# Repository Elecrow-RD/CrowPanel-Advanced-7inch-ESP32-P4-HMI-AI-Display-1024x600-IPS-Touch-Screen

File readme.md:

### 1, Product picture

### 2, Product version number

|      | Hardware | Software | Remark |
| ---- | -------- | -------- | ------ |
| 1    | V1.0     | V1.0     | old |
| 1    | V1.1     | V1.1     | old |
| 1    | V1.2     | V1.2     | latest |

**Version 1.1 Update**

The C6 module version 1.1 adds support for 4-wire SDIO communication. Additionally, the arrangement of the SDIO pins has been adjusted, with the pin mappings of the data lines D0–D3 changing from **IO14, IO15, IO16, IO17** to **IO17, IO16, IO15, IO14**. 

**Version 1.2 Update** 

Based on the V1.1 version, V1.2 further optimized the communication stability of the LoRa wireless module. At the same time, the signal pins of the wireless module socket were re-allocated: the original **IO53 and IO54** were adjusted to **IO27 and IO28** respectively, and correspondingly, **IO27 and IO28** were adjusted to **IO53 and IO54** respectively.

### 3, product information

| **Main Chip-ESP32-P4NRW32**                  |                                                              |
| -------------------------------------------- | ------------------------------------------------------------ |
| CPU/SoC                                      | **ESP32-P4**RISC-V 32-bit dual-core processor for HP systems, running at up to 400 MHz;RISC-V 32-bit single-core processor for LP systems, running at up to 40 MHz |
| System Memory                                | 768 KB L2MEM (HP) 32 KB SRAM (LP) 8 KB TCM 32 MB PSRAM       |
| Memory                                       | 128 KB ROM (HP) 16 KB ROM (LP) 16 MB Flash                   |
| Development Environment                      | ESP-IDF、Arduino IDE                                   |
| **Screen**                                   |                                                              |
| Size                                         | 7.0 inch                                                     |
| Resolution                                   | 1024*600                                                     |
| Display Panel                                | IPS Panel                                                    |
| Touch Panel                                  | Capacitive Touch, Single/5-point Touch                       |
| Viewing Angle                                | 178°                                                         |
| Brightness                                   | 400 cd/m²(Typ.)                                              |
| Color Depth                                  | 16.7M (8-bit)                                                |
| **Wireless Communication - Onboard Antenna** |                                                              |
| WiFi                                         | Support 2.4GHz(Wi-Fi6), 802.11a/b/g/n                        |
| Bluetooth                                    | Support Bluetooth 5.3 and BLE                                |
| Other                                        | Zigbee, LoRa, nRF2401, Matter, Thread (**Optional**)         |
| **Interface/Function**                       |                                                              |
| Interface                                    | USB2.0, UART, I2C, GPIO female headers, SD card holder, battery socket, speaker jack, camera header, module female headers, etc. |
| Function                                     | Audio amplifier, battery charge management, USB to UART, dual microphones, dual speakers etc. |
| **Button/LED Indicator**                     |                                                              |
| Reset Button                                 | Yes, press to reset the device                               |
| Boot Button                                  | Yes, press and hold the power button to burn the program     |
| Power Button                                 | Switch On/Off                                                |
| PWR                                          | Device power on/off indication                               |
| CHG                                          | Lithium battery charging status, Low battery state           |
| **Other**                                    |                                                              |
| Installation method                          | All around mounting holes(M3 3.2mm), embedded, shell assembly |
| Operating temperature                        | -20~70 °C                                                    |
| Storage temperature                          | -30~80 °C                                                    |
| Power Input                                  | 5V/2A, USB or UART terminal                                  |
| Active Area                                  | 155mm*87mm                                                   |
| Dimensions                                   | 180*105mm                                                    |

### Functional description of the product's internal interfaces:

| Pin Name | Description                                                  | Connector Type |
| :------- | :----------------------------------------------------------- | :------------- |
| SPK      | Output audio signals to connect to speakers. The main board comes with a power amplifier chip circuit. | PH2.0-2P       |
| PWR      | Power LED.                                                   |                |
| RST      | Reset button. Press it to reset the system.                  |                |
| boot     |                                                              |                |
| UART1    | Builds communication between Logic modules, including the serial communication module and the print module. | HY2.0-4P       |
| I2C      | Builds communication between Logic modules, including the serial communication module and the print module. | HY2.0-4P       |
| UART3-IN | Input power supply and serial communication functionality    | XH2.54-4P      |
| BAT      | Connect the lithium battery. (with battery charging circuit) | PH2.0-2P       |

### 4, Use the driver module

| Name | dependency library |
| ---- | ------------------ |
| LVGL | lvgl/lvgl@9.2   |

### 5,Quick Start

##### ESP-IDF starts

1.Right-click on an empty space in the project folder and select "Open with VS Code" to open the project.

2.In the IDF plug-in, select the port, then compile and flash

### 6,Folder structure.
|--3D file： Contains 3D model files (.stp) for the hardware. These files can be used for visualization, enclosure design, or integration into CAD software.

|--Datasheet: Includes datasheets for components used in the project, providing detailed specifications, electrical characteristics, and pin configurations.

|--Eagle_SCH&PCB: Contains **Eagle CAD** schematic (`.sch`) and PCB layout (`.brd`) files. These are used for circuit design and PCB manufacturing.

|--example: Provides example code and projects to demonstrate how to use the hardware and libraries. These examples help users get started quickly.

|--factory_firmware: Stores pre-compiled factory firmware that can be directly flashed onto the device. This ensures the device runs the default functionality.

|--factory_sourcecode:  Contains the source code for the factory firmware, allowing users to modify and rebuild the firmware as needed.

|--libraries: Includes necessary libraries required for compiling and running the project. These libraries provide drivers and additional functionalities for the hardware.

### 7,Pin definition

#### ESP32-P4 7 inch and IPS Display Wiring Pins:
**DSI = Display Serial Interface**is a high-speed, low-power display interface standard defined by the MIPI Alliance, most commonly used in smartphones, tablets, Raspberry Pi devices, and embedded Linux systems.

DSI Pin connection

DSI_DATAN0--IO40

DSI_DATAN0--IO39

DSI_DATAN0--IO36

DSI_DATAN0--IO35

DSI_CLKN--IO37

DSI_CLKP--IO38

DSI_REXT--IO34

#### ESP32-P4 and Touch Driver Wiring：

i2c address: 0x5D/0x14.(The INT pin level during reset of the GT911 touch chip determines the device address.)

INT Low Level(0x5D);

INT High Level(0x14).

Pin connection

I2C1_SCL(IO46)

I2C1_SDA(IO45)

INT_TP(IO42)

RESET_TP(IO40)

#### ESP32-P4 and wireless module wiring pins：

Output voltage: 3.3V Output current: 1A max. Use: The power supply communicates with the wireless module.

Pin connection

#define RADIO_GPIO_CLK 8

#define RADIO_GPIO_MISO 7

#define RADIO_GPIO_MOSI 6

#ifdef CONFIG_BSP_SX1262_ENABLED

#define SX1262_GPIO_BUSY 9

#define SX1262_GPIO_IRQ 53

#define SX1262_GPIO_NRST 54

#define SX1262_GPIO_NSS 10

#ifdef CONFIG_BSP_NRF2401_ENABLED

#define NRF24_GPIO_IRQ 9

#define NRF24_GPIO_CE 53

#define NRF24_GPIO_CS 54

ESP32-P4 and Audio out：

Pin connection

#define AUDIO_GPIO_LRCLK    21   // GPIO pin number for LRCLK (Left-Right Clock)

#define AUDIO_GPIO_BCLK     22   // GPIO pin number for BCLK (Bit Clock)

#define AUDIO_GPIO_SDATA    23   // GPIO pin number for SDATA (Serial Data)

#define AUDIO_GPIO_CTRL     30   // GPIO pin number for audio amplifier control

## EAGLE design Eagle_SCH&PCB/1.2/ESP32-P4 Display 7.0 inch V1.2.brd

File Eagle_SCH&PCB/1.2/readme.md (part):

# ESP32-P4 7.0-Inch Display Product Hardware Driver Guide

| Document Attribute | Details |
| --- | --- |
| Document Version | V1.0 |
| Applicable Hardware | ESP32-P4 Display 7.0 inch V1.2 |
| Baseline Date | 2026-07-29 |
| Schematic Date | 2026-05-05 (drawing frame date) |
| Author | OpenAI Codex (compiled from project schematics and validated examples) |
| Document Status | Suitable for hardware maintenance, driver porting, and onboarding handoff |

## 1. Document Scope and Evaluation Criteria

This document cross-checks the following evidence within the project:

1. `1.2/ESP32-P4 Display 7.0 inch V1.2.sch`: EAGLE 9.6.2 schematic source file, used as the primary evidence for components, nets, and electrical connections.
2. `1.2/ESP32-P4 Display 7.0 inch V1.2.pdf`: Single-page full-board schematic, used as visual verification evidence for functional sections, populated/NC markings, and graphical connections.
3. `idf-code/Lesson01` through `Lesson17`: ESP-IDF examples organized by function, used as the primary evidence for working software configurations.
4. The `idf_component.yml`, `Kconfig`, header files, and BSP source files for each example: used as evidence for versions, default values, and build dependencies.

The evidence priority is as follows:

`Effective constants/initialization parameters in working code` > `Kconfig defaults or comments in the same directory` > `V1.2 schematic nets` > `general README`.

When the code and schematic are inconsistent, this document uses the code as the current runtime baseline as required and lists the discrepancies in Section 15. Here, “validated” means that the repository provides the function as a standalone lesson example; it does not mean that the hardware was reconnected and electrically tested during the generation of this document. The repository does not include complete `sdkconfig` files, build artifacts, or test logs, so final values that depend on menuconfig must still be fixed in the production project.

## 2. Product Hardware Architecture

The product uses the ESP32-P4NRW32 as the main application controller, while the ESP32-C6-MINI-1-N4 provides Wi-Fi/wireless coprocessing capabilities. The main controller connects directly to the 7-inch MIPI-DSI display, MIPI-CSI camera interface, touch I2C, SDMMC, PDM microphone, I2S amplifiers, USB 2.0, and UART/I2C/GPIO expansion interfaces. The board also includes an STC8H1K08 for auxiliary control functions such as charging-status and battery monitoring.

The main onboard power paths include USB/5 V input, battery charging and power switching, 5 V-to-3.3 V conversion, 5 V-to-1.2 V conversion, a 3.3 V audio LDO, 2.8 V/1.8 V camera LDOs, LCD power, and a boost/constant-current backlight driver.

## 3. Peripheral Overview

| Category | Device/Interface | Key Connection or Model | Software Validation Status |
| --- | --- | --- | --- |
| Main controller | ESP32-P4NRW32 (U7) | External W25Q128JVSIQ, 40 MHz, 32.768 kHz | Validated; target of all ESP-IDF examples |
| Wireless coprocessor | ESP32-C6-MINI-1-N4 (IC1) | P4 GPIO47/48 UART; GPIO32 enable; C6 SDIO network present | Wi-Fi example available; underlying P4-C6 transport abstraction is not fully included in the repository |
| Display | 7.0-inch 1024x600 IPS + EK79007 | 2-lane MIPI-DSI, GPIO31 backlight | Validated |
| Touch | GT911 capacitive touch | I2C0 GPIO45/46, RST40, INT42 | Validated |
| Camera | SC2336 (software detection target)/24-pin CSI FPC | 2-lane MIPI-CSI, SCCB GPIO12/13 | Validated |
| Storage | W25Q128JVSIQ NOR Flash | Dedicated ESP32-P4 Flash pins | Boot storage, managed by ESP-IDF |
| Storage | MicroSD card socket | Schematic: SDMMC GPIO14..19; code: GPIO43/44/39 | Validated code differs from schematic; see Section 15 |
| Audio input | LMA3526B381-class PDM microphone (U176) | CLK24, DATA26, L/R20 | Validated |
| Audio output | Dual NS4168 (U13/U3) + dual speakers | I2S GPIO21/22/23, SD GPIO30 | Validated |
| Optional audio codec | ES7210 ADC, ES8311 DAC | Explicitly marked `NC` in schematic | Must not be enabled by default |
| USB Device | ESP32-P4 USB 2.0 D+/D- | Native TinyUSB HID | Validated |
| USB-to-UART | CH340K (U1) | Onboard download/debug channel | Fixed hardware function; no application driver |
| UART expansion | UART1/UART2/UART3 nets | GPIO47/48, 34/33, 27/28, etc. | UART2 code validated |
| I2C expansion | 4-pin I2C_OUT | GPIO45/46 level-shifted to 3.3 V through BSS138 | Bus driver validated |
| GPIO expansion | 2x12 J7 | GPIO2/3/4/5/25/49..54, 3.3 V/5 V/GND | No unified driver; available for peripheral reuse |
| Environmental sensor | DHT20 (external) | I2C 0x38, shared GPIO45/46 | Example validated; not an onboard device |
| LoRa | SX1262 (external) | SPI GPIO6/7/8 + control pins | TX/RX examples validated; control-pin version conflict exists |
| 2.4 GHz | nRF24 (external) | SPI GPIO6/7/8 + control pins | TX/RX examples validated; control-pin version conflict exists |
| Charging management | TP4059-SOT23-6 (U2) | 5 V, battery, CHG/STDBY status | Automatic hardware function; monitored by STC8 |
| Auxiliary MCU | STC8H1K08-36I (U14) | Charging LED, status, ADC_VBAT, UART | Present in schematic; repository contains no STC8 firmware |
| Power | MT3406 x2, MT9201, MT3608, ME6211 series | 3.3 V, 1.2 V, LCD/backlight, camera/audio power | Automatic hardware function/enable-pin controlled |
| Buttons/switches | BOOT K3, RESET K4, power slide switch SW1 | BOOT/CHIP_PU/power MOSFET | Fixed hardware function |
| Indicators | Charging/full/power LEDs | TP4059 + STC8/discrete logic | Repository contains no application-level LED driver |

## 4. ESP32-P4 GPIO Resource Table

The table below prioritizes the values actually used by the code; “Schematic Function” is provided to identify electrical connections.

| GPIO | Current Code Function | Direction/Multiplexing | Schematic Net/Electrical Connection | Conflict Notice |
| ---: | --- | --- | --- | --- |
| 6 | Wireless SPI MOSI | SPI output | Wireless interface series resistor | Shared by wireless modules |
| 7 | Wireless SPI MISO | SPI input | Wireless interface series resistor | Shared by wireless modules |
| 8 | Wireless SPI SCK | SPI output | Wireless interface series resistor | 8 MHz |
| 9 | SX1262 BUSY / nRF24 IRQ | Input/interrupt | Wireless interface | The two modules are mutually exclusive |
| 10 | SX1262 NSS | Push-pull output | Wireless interface | nRF24 code does not use this pin |
| 11 | Camera RESET net | GPIO output through level shifter | `IO11_CSI_RESET` | Current camera code instead configures `reset_pin=-1` |
| 12 | Camera SCCB SDA | I2C open-drain | `I2C2_SDA` through BSS138 | Code enables internal pull-up |
| 13 | Camera SCCB SCL | I2C open-drain | `I2C2_SCL` through BSS138 | 100 kHz |
| 14..19 | Onboard SDMMC D3/D2/D1/D0/CLK/CMD in schematic | SDMMC | Directly connected to SD card nets | Not used by current SD code |
| 20 | PDM microphone L/R selection | GPIO/strap | `MIC_L/R` | Current code does not actively set it; channel is determined by hardware resistor |
| 21 | Audio LRCLK | I2S1 output | Dual NS4168 LRCLK | 16 kHz |
| 22 | Audio BCLK | I2S1 output | Dual NS4168 BCLK | Standard I2S |
| 23 | Audio SDATA | I2S1 output | Dual NS4168 SDATA | 16-bit stereo |
| 24 | PDM CLK | I2S0 output | PDM microphone CLK; also routed to optional codec MCLK | Occupied during recording |
| 26 | PDM DATA | I2S0 input | PDM microphone DATA | Occupied during recording |
| 27 | SX IRQ / UART TX (code) | Interrupt input/output | Schematic net is `P4_TXD2` | Conflicts with GPIO53 Kconfig default |
| 28 | SX RESET / nRF CS / UART RX (code) | Output/input | Schematic net is `P4_RXD2` | Multiple functions are mutually exclusive; conflicts with GPIO54 Kconfig default |
| 29 | LCD backlight power control | GPIO output | `LCD_BK_POWER`, Q11 marked NC | Not driven by current display code |
| 30 | Audio amplifier SD | Push-pull output, active-low enable | `AUDIO_OUT_SD` -> Q10 -> dual amplifier CTRL | Validated |
| 31 | LCD backlight brightness | LEDC PWM | `LCD_BK_EN` -> MT9201 EN | 30 kHz, 11-bit |
| 32 | ESP32-C6 EN | Push-pull output/reset | `C6_EN` | Requires attention when powering up the Wi-Fi subsystem |
| 33 | Expansion UART RX | UART input | `RXD3` through level shifter | UART_IN_RXD3 on the 5 V side |
| 34 | Expansion UART TX | UART output | `TXD3` through level shifter | UART_IN_TXD3 on the 5 V side |
| 37 | Debug/download TXD0 | UART output | `TXD0` | CH340K path |
| 38 | Debug/download RXD0 | UART input | `RXD0` | CH340K path |
| 39 | SD D0 (code) | SDMMC input/output | Schematic only shows `P4_IO39` through series resistor | Inconsistent with onboard SD schematic |
| 40 | GT911 RESET | Push-pull output, active-low | `RESET_TP` | Validated |
| 41 | LCD RESET | Push-pull output, active-low | `LCD_RESET` | Display driver sets `reset_gpio_num=-1`; handled by hardware/panel path |
| 42 | GT911 INT | Input/touch-address strap | `INT_TP` | Driver interrupt level configured as 0 |
| 43 | SD CLK (code) | SDMMC output | Schematic only shows `P4_IO43` | Inconsistent with onboard SD schematic |
| 44 | SD CMD (code) | SDMMC bidirectional | Schematic only shows `P4_IO44` | Inconsistent with onboard SD schematic |
| 45 | GT911/expansion I2C SDA | I2C0 open-drain | `I2C1_SDA`, through BSS138 to the 3.3 V side | Shared bus |
| 46 | GT911/expansion I2C SCL | I2C0 open-drain | `I2C1_SCL`, through BSS138 to the 3.3 V side | 400 kHz |
| 47 | ESP32-C6/UART2 TX | UART output | `TXD1` | 115200 8N1 example |
| 48 | ESP32-C6/UART2 RX | UART input | `RXD1` | 115200 8N1 example |
| 49..52 | J7 GPIO expansion | General-purpose GPIO | Directly connected to J7 | Pay attention to external loads |
| 53/54 | J7 GPIO / default wireless Kconfig control pins | General-purpose GPIO | Directly connected to J7 | Actual code headers do not use Kconfig values |

MIPI DSI, MIPI CSI, USB D+/D-, external Flash, crystal, and ESP32-P4 internal power pins are dedicated pins. They are not included in the general-purpose GPIO table and must not be repurposed as general-purpose I/O.

## 5. Main Controller, Boot, and External Flash

### 5.1 ESP32-P4NRW32

- Main controller: U7, ESP32-P4NRW32, RISC-V application processor.
- Software layer: ESP-IDF + FreeRTOS; the display/touch functions use Espressif Component Manager components.
- Minimum dependency: Multiple examples specify ESP-IDF `>=5.4.0`; the display lesson specifies `>=5.4.2`.
- Boot: K3 pulls `SPI_BOOT` low to enter download mode; K4 pulls `CHIP_PU` low to reset.
- Clocks: 40 MHz main crystal; 32.768 kHz low-speed crystal.

### 5.2 W25Q128JVSIQ

- The dedicated U7 `FLASH_CS/CK/WP/HOLD/D/Q` pins connect to the IC10 W25Q128JVSIQ.
- The driver is managed by the ESP-IDF ROM bootloader, SPI Flash driver, and partition table. It must not be reinitialized at the application layer using a general-purpose SPI driver.
- Partitions: Each lesson project includes its own `partitions.csv`; when porting to a unified product project, a single partition baseline must be selected.
- Risk: Do not reuse dedicated Flash pins. Before changing the Flash frequency/mode, verify `menuconfig` and the device capabilities.

## 6. Display and Backlight

### 6.1 EK79007 MIPI-DSI Display

| Parameter | Validated Code Value |
| --- | --- |
| Resolution | 1024 x 600 |
| Pixel format | RGB565, 16 bpp |
| DSI | bus 0, 2 data lanes, 900 Mbps/lane |
| DPI pixel clock | 51 MHz |
| Horizontal timing | BP 160, pulse 70, FP 160 |
| Vertical timing | BP 23, pulse 10, FP 12 |
| DBI commands | 8-bit command, 8-bit parameter, VC0 |
| Frame buffer | 1 panel FB; LVGL uses double buffering in SPIRAM |
| Rotation | No XY swap or mirroring |

Software dependencies: `esp_lcd_mipi_dsi`, `espressif/esp_lcd_ek79007 ^1.0.2`, `espressif/esp_lvgl_port ^2.6.0`, `lvgl ^8.3.11`, FreeRTOS.

Key configuration example:

```c
esp_lcd_dsi_bus_config_t bus = {
    .bus_id = 0,
    .num_data_lanes = 2,
    .lane_bit_rate_mbps = 900,
};
esp_lcd_dpi_panel_config_t dpi = {
    .dpi_clock_freq_mhz = 51,
    .pixel_format = LCD_COLOR_PIXEL_FORMAT_RGB565,
    .video_timing = { .h_size = 1024, .v_size = 600,
        .hsync_back_porch = 160, .hsync_pulse_width = 70, .hsync_front_porch = 160,
        .vsync_back_porch = 23, .vsync_pulse_width = 10, .vsync_front_porch = 12 },
};
```

Initialization sequence: backlight PWM initialization -> DSI bus -> DBI IO -> EK79007 panel reset/initialization -> LVGL port -> first-frame rendering -> turn on backlight. The code explicitly keeps the backlight off at the end of `display_init()`; the caller must subsequently invoke `set_lcd_blight()`.

### 6.2 Backlight

- GPIO31, GPIO push-pull + LEDC low-speed channel 0, timer 0.
- 30 kHz, 11-bit, PLL divided clock.
- The brightness interface accepts 0..100; the actual nonzero duty is `brightness * 18 + 200`, so it is not a strict percentage.
- Electrical path: GPIO31 -> MT9201 EN/dimming path -> DSI LED driver; the schematic specifies an LED current of approximately 182 mA (`200 mV / 1.1 ohm`).
- Risk: Do not configure GPIO31 as a regular GPIO held high for extended periods and thereby bypass the PWM constraints. Changing the backlight current requires modifying the hardware sense resistor, not merely changing the duty cycle.

## 7. GT911 Touch

- GPIO45 SDA, GPIO46 SCL, I2C master port 0, 7-bit address.
- Bus frequency: 400 kHz; I2C glitch filter: 7 cycles. The code enables the SoC internal pull-ups, while the schematic also includes level shifting/external pull-up networks.
- GPIO40 RESET, active-low; GPIO42 INT, with the driver configured for interrupt level=0.
- Resolution bounds: 1024x600; no XY swap or mirroring.
- Address: First uses `ESP_LCD_TOUCH_IO_I2C_GT911_ADDRESS`; if that fails, it tries `..._ADDRESS_BACKUP`, supporting both GT911 address-strap states.
- Software layer: ESP-IDF new I2C master API, `esp_lcd_panel_io_i2c`, `esp_lcd_touch_gt911`, FreeRTOS.

Initialization sequence: `i2c_init()` -> create panel I/O -> `esp_lcd_touch_new_i2c_gt911()` -> periodically call `touch_read()`. The USB HID example reads at 10 ms intervals, corresponding to an application sampling rate of 100 Hz.

Note: Before switching to the backup address after a failure, the current code does not delete the panel I/O handle created during the first attempt. For long-term maintenance, unified failure cleanup is recommended; this issue does not change the existing working parameters.

## 8. MIPI-CSI Camera

### 8.1 Electrical Connections

- 24-pin FPC3, 2-lane MIPI-CSI: D0+/D0-, D1+/D1-, CLK+/CLK-.
- SCCB: GPIO12 SDA, GPIO13 SCL, through BSS138 level shifting.
- Schematic: GPIO11 connects to `CSI_RESET` through a level shifter; the FPC also provides XVCLK, AVDD_2V8, and DOVDD_1V8.
- Software identification/tuning file: SC2336, 50 Hz anti-flicker.

### 8.2 Driver Configuration

- SCCB master port 1, 100 kHz, with internal pull-ups enabled.
- `esp_video_init()` reuses the previously created I2C bus handle.
- `reset_pin=-1`, `pwdn_pin=-1`; the current code does not operate the GPIO11 reset shown in the schematic.
- V4L2 device: `ESP_VIDEO_MIPI_CSI_DEVICE_NAME`, opened as nonblocking and read-only.
- Output format: forced to RGB565; the resolution is negotiated by the current sensor/V4L2 mode and is not hard-coded in the BSP.
- Two cache-aligned SPIRAM user-pointer buffers using V4L2 `REQBUFS/QUERYBUF/QBUF`; the capture task is pinned to core 0 at priority 3.
- Software dependencies: `esp_cam_sensor ^1.2.0`, `esp_sccb_intf ^0.0.5`, `esp_video ^1.1.0`, V4L2, LVGL, SPIRAM.

Initialization sequence: SCCB bus -> `esp_video_init()` -> open CSI device -> query/set RGB565 -> allocate and queue double buffers -> create LVGL canvas -> stream on.

Risk: Camera power and reset timing currently depend on board-level hardware/default driver behavior. If the sensor is replaced or intermittent detection failures occur during cold startup, add the GPIO11 reset sequence and a power-stabilization delay before attempting to increase the SCCB frequency.

## 9. SD Card

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
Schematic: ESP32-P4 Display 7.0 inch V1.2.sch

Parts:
C1, C2, C3, C17, C22, C69, C86, C102: 1uF; 0603
C4: 10uF/NC; 0603
C5, C7, C9, C36, C40, C41, C43, C45, C46, C50, C60, C61, C63, C72, C73, C108, C113, C115: 100nF; C0402
C6, C8, C42, C44, C47, C48, C49, C56, C71, C107, C112, C114, C116: 10uF; C0402
C10: 1uF; DISCRETE-NEW_C0603
C11, C15, C19, C20, C21, C35, C37, C52, C53, C54, C75, C76, C77, C80, C81, C82, C84, C144, C150, C151, C152, C155, C156, C159, C169: 100nF; 0603
C12, C27, C28, C32: 10uF/10V+; 0603
C13, C18: 22uF; C0805
C14, C16, C38, C74, C78, C79, C83, C136, C149, C153, C157: 10uF; 0603
C23, C24, C103, C104: 47uF; 0603
C25, C160, C161, C162, C163, C164, C165, C166, C167, C168: 10pF_NC; C0402
C26, C31: 22pF; 0603
C29, C30: 12pF; C0402
C33, C34: 15pF; C0402
C39, C130, C132, C145: 100nF_NC; C0402
C51, C55, C57, C58, C59, C64, C65, C66: 1uF; C0402
C62: 10nF; C0402
C67, C68, C85, C105, C106, C158: 1nF; 0603
C70: 10UF; 0603
C87: 15pF; 0603
C88: 10UF_NC; 0603
C89, C101: 22pF_NC; C0402
C90, C99, C110: 10uF/25V; 0603
C91, C100, C111: 100nF/50V; 0603
C92: 22uF/16V; C0805
C93: 10nF/25V; 0603
C94: 10uF/25V; C0402
C95: 100nF/50V; C0402
C96, C97: 1uF/25V; 0603
C98, C109: 1uF/50V; 0603
C117, C118, C119, C120, C121, C122, C123, C124, C125, C126, C127, C128, C129, C131, C133, C137, C138, C139, C140, C141, C142, C146: 1uF_NC; C0402
C134, C148: 47uF_NC; 0603
C135, C147, C154: 100nF_NC; 0603
C143: 1uF_NC; 0603
C170, C171, C172, C173, C174, C175, C176: NC; C0402
D1: KT-0603RYG; LED_KT-0603RYG
D2, D007, D10: DSS34; D_SOD123FL
D003: NC/DSS34; D_SOD123FL
D4, D008, D11: 1N5817WS; D_SOD323
D005, D012, D013, D015, D017, D018: LMBR140ET1G
D14: Red; LED0603
D016: MM1W18_18V; LMSZ5233BT1G
D020: LMSZ5233BT1G_-6V; LMSZ5233BT1G
FB2, FB3, FB10, FB11: 1K/磁珠; L0603
FB4, FB5, FB13: 0R/800mA_NC; L0402
FB6: 0R/800mA; L0402
FB7, FB8, FB9, FB12: 1K/磁珠_NC; L0603
FB14: 0R/800mA_NC; R0402
FB15, FB16: 0R/800mA_NC; L0603
FB17, FB18, FB19, FB20: 0R/800mA; L0603
FB21: 0R/800mA; L0805
FPC2: FPC-6PIN-0.5MM
FPC3: AFC24-S24FIA-00; FPC-SMD_P0.50-24P_QCHF-SM-H2.0
IC1: ESP32-C6-MINI-1-N4; ESP32C6MINI1N4
IC2: ME6211C18M5G-N; SOT95P282X145-5N
IC3: ME6211C28M5G-N; SOT95P282X145-5N
IC4: ME6211C18M5G-N_NC; SOT95P282X145-5N
IC5: ES7210_NC; QFN40P400X400X80-33N
IC6: ES8311_NC; QFN40P300X300X60-21N
IC7, IC8: ME6211C33M5G-N; SOT95P282X145-5N
IC10: W25Q128JVSIQ; SOIC127P790X216-8N
J1, J16: TYPEC-3.0-16P-SMD; USB-3.0TYPEC-SMD
J2, J13: HY2.0-4P-SMT; CONNECTOR_4P-SMD-2.0
J3, J4, J6: PH2.0WT-2PIN
J5: HOLDER-MICROSD-9P; 9P-SMD-W/-RING
J7: CONN_12X22X12-SMD1; 2X12-SMD1
J8: HC-PZ200-8.7L-1X4PZ1; TEST-PIN-4-2.0MM
J9, J11: HEADER-7P-18.28X2.5; H7-2.54-18.28X2.5X5MM
J10: XH2.54-4P-SMT; XH2.54-4P-SMD
J12, J14, J15, J18: THO-M3.25MM-HOLE; THO-M3.2*5MM-HOLE
J21: C23398852_30P_0.5MM_下接_FC-05A30P11H20
K3, K4: KEY-4.5X4.5; KEY-4.5X4.5-SMD
L1, L6: 2.2μH_C5179446; 1008(2520)
L2, L5: 4.7uH_C45385206_2.4A; 1008(2520)
L3: 0R; L0603
L4: NC; L0603
P1, P2, P3, P4, P5, P6, P7, P8, P9, P10, P11, P12, P13, P14, P15, P17, P18, P19, P20, P21, P24, P25, P26, P28, P31, P32, P33, P34, P35, P36, P37, P38, P39, P53, P54, P55, P56, P57, P63, P64, P65, P66, P67, P68, P77, P87, P88: TEST_PADPAD-1.5MM; TEST_PAD-1.5MM
Q1, Q2, Q4, Q6, Q7, Q8, Q9: BSS138W_SOT323; MOS_SOT323
Q3, Q5: NCE20P45Q; PDFN3333
Q10: AO3401; PMOS_SOT23
Q11: AO3401_NC; PMOS_SOT23
R1, R5, R9, R18, R53, R54, R61, R66, R67, R71, R77, R87, R91, R106, R116, R160, R180, R181: 10K; R0603@1
R2, R117, R139, R165: 100K; R0603@1
R3, R4, R17, R26, R47, R50, R96, R101: 5.1K; R0603@1
R6, R7, R8, R10, R13, R24, R55, R60, R65, R76, R103, R118, R119, R184, R188, R189: 0R; R0603@1
R11: 22.1K; R0603
R12, R19, R20, R36, R37, R38, R39, R40, R41, R42, R43, R44, R70, R80, R88, R89, R90, R92, R95, R99, R100, R102, R105, R109, R190: 0R; R0402
R14, R21: NC/499K; R0603
R15, R27, R28, R29, R30, R140: 10K; 0402
R16, R31, R32, R69: 2K; R0603-SP
R22, R45, R46, R51, R52, R56, R57, R58, R59, R62, R78: 4.7K; R0603@1
R23: 0R; C0402
R25: 0R; R0603-SP
R33: 10K_NC; 0402
R34, R48, R49, R133, R135, R136, R137, R138: 22R; 0402
R35: NC/10M; R0402
R63, R64, R68, R108, R122, R123: 100K; R0402
R72, R73: 10K_NC; R0402
R74, R93, R94, R97, R98: 2K; R0603@1
R75: 2K_NC; R0603@1
R79, R147, R185: OR_NC; R0603-SP
R81, R82, R83, R84, R85, R86: 51K; 0402
R104, R158: 4.02K; R0402
R107, R110, R111, R124, R125, R126, R128, R130, R146, R148, R161, R170, R177: 0R_NC; R0402
R112, R113, R114, R115, R129, R149: 22R; R0603@1
R120, R121: 5.1K_NC; R0603@1
R127, R162: 22R; R0402
R131, R171, R333: 10K; R0402
R132, R134: OR; R0402
R141, R142, R144, R145: OR_NC; R0402
R143: 51K; R0603-SP
R150, R151, R216, R217, R332: 0R; 0402
R152, R153, R154, R155, R156, R157: 100R; R0402
R159: 1.1R; R0603-SP
R163: NC; R0603-SP
R164: 39k; R0603@1
R166: 180K; R0603
R167: 12K; R0603
R168: 1.91K; R0402
R169: 1K; R0402
R172, R174: 220R; R0603
R173, R175: 51K; R0603@1
R178, R179: 20K_NC; R0603
R182: 0R; L0805
R186: 100k; R0603@1
R187: 10k; R0603@1
R210: NC/10K; R0603@1
SW1: switch_6pin; SWITCH_6PIN_2P
U1: CH340K; ESOP-10-EP-150MIL
U2: TP4059-SOT23-6; SOT23-6L
U3, U13: NS4168; NS4168-ESOP-8
U4: NS4263B; SOP16
U6: MT9201; COOPER_SOT23-6
U7: ESP32-P4NRW32; IC_ESP32-P4NRW32
U8: UMH3NTN; SOP65P210X100-6N
U9, U10: MT3406_C22462728; SOT95P280X145-5N
U14: STC8H1K08-36I; TSSOP20
U16: MT3608; SOT95P280X145-6N
U176: LMA3526B381; MIC-SMD_5P-L3.5-W2.7-P1.67
Y2: 40MHZ; X322540MPB4SI
Y3: 24Mhz; 24MHZ_1631-24003-BTKEYA
Y4: 32.768K; NORDIC_NRF_XTAL_3215_N

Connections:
3V3$: C2.2, U1.10 (V3)
13: R189.2, U14.3 (MISO/P1.4)
14: R188.2, U14.4 (SCLK/P1.5)
+5V_IN: D2.+, D4.+, J10.3, P66.P$1, R46.1, R51.1
+VBUS1: D10.+, D11.+, J1.A4, J1.A9, J1.B4, J1.B9, P1.P$1
+VBUS2: D007.+, D008.+, J16.A4, J16.A9, J16.B4, J16.B9, P87.P$1
ADC_AVDD_3V3: C132.1, C133.2, FB5.2, IC5.22 (VDDA), IC5.23 (VDDM)
ADC_DVDD_3V3: C130.1, C131.2, FB4.2, IC5.6 (VDDP), IC5.7 (VDDD), R73.1
ADC_VBAT: C158.2, R164.2, R186.1, U14.13 (P3.2/ADC10)
AGND: C102.2, C103.2, C104.2, C105.1, C106.1, C134.1, C143.1, C148.1, C154.2, FB19.2, FB21.2, J4.P$3, J4.P$4, R79.2, R143.1, R185.1, U4.2, U4.7, U4.15, U13.7 (GND), U13.9 (PE)
AGND1: C72.1, C117.1, C118.1, C119.1, C120.1, C121.1, C122.1, C127.2, C128.2, C129.2, C132.2, C133.1, C137.1, C138.2, C139.2, C142.2, IC5.21 (GNDA), IC6.10 (AGND), R144.1, R145.2, R171.2, R182.2, U176.5_1 (5), U176.5_2 (5)
AGND3: C22.2, C23.2, C24.2, C67.1, C68.1, FB20.2, J6.P$3, J6.P$4, U3.7 (GND), U3.9 (PE)
AUDIO_CTRL: Q10.3 (D), R117.2, R139.2
AUDIO_OUT_5V: C134.2, C148.2, C154.1, FB15.2, U4.4, U4.13
AUDIO_OUT_SD: Q10.1 (G), R71.1, R147.1, U7.60 (GPIO30)
AUDIO_VDD1: C102.1, C103.1, C104.1, FB17.1, U13.6 (VDD)
AUDIO_VDD2: C22.1, C23.1, C24.1, FB18.1, U3.6 (VDD)
AUDIO_VDD_3V3: C152.2, C153.2, FB4.1, FB5.1, FB6.1, FB14.1, FB16.2, IC7.5 (VOUT)
AVDD_2V8: C82.2, C83.2, FPC3.1, FPC3.2, IC3.5 (VOUT)
C6_EN: C15.1, IC1.8 (EN), P37.P$1, R77.1, U7.63 (GPIO32)
C6_IO8: IC1.22 (IO8), R87.2
C6_IO9_BOOT: IC1.23 (IO9), P36.P$1
C6_RXD0: IC1.30 (RXD0), P21.P$1
C6_SD2_CLK: C25.2, IC1.25 (IO19), R34.2, R82.2
C6_SD2_CMD: C160.2, IC1.24 (IO18), R81.2, R133.2
C6_SD2_D0: C161.2, IC1.26 (IO20), R83.2, R135.2
C6_SD2_D1: C162.2, IC1.27 (IO21), R84.2, R136.2
C6_SD2_D2: C163.2, IC1.28 (IO22), R85.2, R137.2
C6_SD2_D3: C164.2, IC1.29 (IO23), R86.2, R138.2
C6_TXD0: IC1.31 (TXD0), P25.P$1
C6_VDD_3V3: C11.1, C14.2, IC1.3 (3V3), R76.1, R77.2, R81.1, R82.1, R83.1, R84.1, R85.1, R86.1, R87.1
CODEC_3V3: C145.1, C146.2, FB13.2, FB14.2, IC6.3 (PVDD), IC6.4 (DVDD)
CSID0_P: R153.1, U7.43 (CSI_DATAP0)
CSI_CLK_N: FPC3.19, R156.2
CSI_CLK_P: FPC3.18, R157.2
CSI_D0_N: FPC3.16, R152.2
CSI_D0_P: FPC3.15, R153.2
CSI_D1_N: FPC3.22, R154.2
CSI_D1_P: FPC3.21, R155.2
CSI_RESET: FPC3.8, Q4.2 (S), R57.2
CSI_SCL: FPC3.4, Q7.2 (S), R62.2
CSI_SDA: FPC3.5, Q6.2 (S), R56.2
DA1: J5.8 (DATA1), P56.P$1, R15.1
DA2: J5.1 (DATA2), P53.P$1, R30.1
DOVDD_1V8: C77.2, C78.2, C84.2, C85.2, FPC3.9, IC2.5 (VOUT), Q4.1 (G), Q6.1 (G), Q7.1 (G), R56.1, R57.1, R62.1, R67.2, Y3.4 (4_VDD)
DOWNLOAD_BOOT: R60.1, R106.2
DSI_CLK_N: J21.18, R100.1
DSI_CLK_P: J21.17, R102.1
DSI_DATA0_N: J21.24, R190.1
DSI_DATA0_P: J21.23, R92.1
DSI_DATA1_N: J21.21, R95.1
DSI_DATA1_P: J21.20, R99.1
DTR: R5.2, U1.4 (DTR#), U8.4 (E2)
EN_DCDC: R13.2, U7.79 (EN_DCDC)
ESP32_LDO1: C58.1, R105.2, U7.71 (VFB1/VO1)
ESP32_LDO2: C57.1, R40.2, U7.72 (VFB2/VO2)
ESP32_LDO3: C59.1, R80.2, U7.73 (VFB3/VO3)
ESP32_LDO4: C66.1, R109.2, U7.74 (VFB4/VO4)
FB_DCDC: C31.1, R14.2, R21.1, R103.1, U10.5 (FB)
FLASH_CK: IC10.6 (CLK), U7.32 (FLASH_CK)
FLASH_CS: IC10.1 (/CS), R333.1, U7.27 (FLASH_CS)
FLASH_D: IC10.5 (DI_(IO0)), U7.33 (FLASH_D)
FLASH_HOLD: IC10.7 (/HOLD_OR_/RESET_(IO3)), U7.31 (FLASH_HOLD)
FLASH_Q: IC10.2 (DO_(IO1)), U7.28 (FLASH_Q)
FLASH_WP: IC10.3 (/WP_(IO2)), U7.29 (FLASH_WP)
GND: C1.1, C2.1, C3.1, C4.1, C5.2, C6.1, C7.2, C8.1, C9.2, C10.1, C11.2, C12.2, C13.2, C14.1, C15.2, C16.1, C17.1, C18.2, C19.2, C20.1, C21.1, C25.1, C27.1, C28.2, C29.2, C30.2, C32.1, C33.2, C34.1, C35.1, C36.2, C37.1, C38.1, C39.2, C40.2, C41.2, C42.1, C43.2, C44.1, C45.2, C46.2, C47.1, C48.1, C49.1, C50.2, C51.2, C52.1, C53.1, C54.1, C55.2, C56.1, C57.2, C58.2, C59.2, C60.2, C61.2, C62.2, C63.2, C64.2, C65.2, C66.2, C69.1, C70.2, C71.1, C73.2, C74.1, C75.1, C76.1, C77.1, C78.1, C79.1, C80.1, C81.1, C82.1, C83.1, C84.1, C85.1, C86.1, C87.1, C88.2, C90.2, C91.2, C92.2, C94.2, C95.2, C98.2, C99.2, C100.2, C107.1, C108.2, C109.2, C110.2, C111.2, C112.1, C113.2, C114.1, C115.2, C116.1, C130.2, C131.1, C136.1, C144.1, C145.2, C146.1, C149.1, C150.1, C151.1, C152.1, C153.1, C155.1, C156.1, C157.1, C158.1, C159.1, C160.1, C161.1, C162.1, C163.1, C164.1, C165.1, C166.1, C167.1, C168.1, C169.2, C170.1, C171.1, C172.1, C173.1, C174.1, C175.1, C176.1, D14.-, D016.2, D018.1, D020.1, FB19.1, FB20.1, FB21.1, FPC2.4, FPC2.7, FPC2.8, FPC3.3, FPC3.6, FPC3.10, FPC3.12, FPC3.17, FPC3.20, FPC3.25, FPC3.26, IC1.1 (GND_1), IC1.2 (GND_2), IC1.11 (GND_3), IC1.14 (GND_4), IC1.36 (GND_5), IC1.37 (GND_6), IC1.38 (GND_7), IC1.39 (GND_8), IC1.40 (GND_9), IC1.41 (GND_10), IC1.42 (GND_11), IC1.43 (GND_12), IC1.44 (GND_13), IC1.45 (GND_14), IC1.46 (GND_15), IC1.47 (GND_16), IC1.48 (GND_17), IC1.49 (GND_18), IC1.50 (GND_19), IC1.51 (GND_20), IC1.52 (GND_21), IC1.53 (GND_22), IC1.54 (GND_23), IC1.55 (GND_24), IC1.56 (GND_25), IC1.57 (GND_26), IC1.58 (GND_27), IC1.59 (GND_28), IC1.60 (GND_29), IC1.61 (GND_30), IC2.2 (VSS), IC3.2 (VSS), IC4.2 (VSS), IC5.8 (GNDD), IC5.33 (EP), IC6.5 (DGND), IC6.20 (CE), IC6.21 (EP), IC7.2 (VSS), IC8.2 (VSS), IC10.4 (GND), J1.A1, J1.A12, J1.B1, J1.B12, J1.P$1, J1.P$2, J1.P$3, J1.P$4, J2.4, J2.SS1, J2.SS2, J3.P$2, J3.P$3, J3.P$4, J5.6 (VSS), J5.G1, J5.G2, J5.G3, J5.G4, J7.7, J7.8, J7.10, J7.21, J7.22, J7.23, J7.24, J8.4, J9.6, J9.6-6 (6), J10.4, J10.5 (SS1), J10.6 (SS2), J12.P$1, J13.4, J13.SS1, J13.SS2, J14.P$1, J15.P$1, J16.A1, J16.A12, J16.B1, J16.B12, J16.P$1, J16.P$2, J16.P$3, J16.P$4, J18.P$1, J21.10, J21.13, J21.16, J21.19, J21.22, J21.25, J21.31, J21.32, K3.1, K4.1, P4.P$1, P10.P$1, P12.P$1, P14.P$1, P28.P$1, P31.P$1, P65.P$1, P88.P$1, R3.1, R4.2, R11.2, R16.1, R18.1, R21.2, R33.2, R64.1, R72.1, R96.1, R101.2, R104.1, R108.1, R123.1, R158.2, R159.1, R160.2, R163.1, R167.1, R169.1, R173.1, R175.1, R182.1, R186.2, SW1.1 (1_2B), SW1.6 (6_1B), U1.3 (GND), U1.EP, U2.2 (GND), U6.2 (2-GND), U7.105 (GND), U9.2 (GND), U10.2 (GND), U14.10 (GND), U16.2 (2_GND), Y2.2 (GND_1), Y2.4 (GND_2), Y3.2 (2_GND)
I2C1_SCL: FPC2.1, Q9.2 (S), R97.2, U7.88 (GPIO46)
I2C1_SCL_3V3: IC6.1 (CCLK), J11.2, J11.2-2 (2), J13.1, Q9.3 (D), R93.2, R125.1, R188.1
I2C1_SDA: FPC2.2, Q8.2 (S), R98.2, U7.87 (GPIO45)
I2C1_SDA_3V3: IC6.19 (CDATA), J11.3, J11.3-3 (3), J13.2, Q8.3 (D), R94.2, R124.1, R189.1
I2C2_SCL: Q7.3 (D), R59.2, U7.14 (GPIO13)
I2C2_SDA: Q6.3 (D), R22.2, U7.13 (GPIO12)
I2SOUT_LRCK1: R149.2, U13.2 (LRCLK)
I2SOUT_LRCK2: P35.P$1, R114.2, U3.2 (LRCLK)
I2SOUT_SCLK1: R129.2, U13.3 (BCLK)
I2SOUT_SCLK2: P34.P$1, R113.2, U3.3 (BCLK)
I2SOUT_SD1: R112.2, U13.4 (SDATA)
I2SOUT_SD2: P33.P$1, R115.2, U3.4 (SDATA)
I2S_LRCK: R114.1, R130.1, R149.1, U7.23 (GPIO21)
I2S_LRCK_N: IC5.10 (LRCK), IC6.8 (LRCK), R130.2
I2S_MCLK: R126.1, R127.1, U7.52 (GPIO24)
I2S_MCLK_N: IC5.5 (MCLK), IC6.2 (MCLK), R126.2
I2S_SCLK: R113.1, R128.1, R129.1, U7.24 (GPIO22)
I2S_SCLK_N: IC5.9 (SCLK), IC6.6 (SCLK/DMIC_SCL), R128.2
I2S_SDIN1_N: IC5.11 (SDOUT1/TDMOUT)
I2S_SDIN2: R161.1, R162.1, U7.55 (GPIO26)
I2S_SDIN2_N: IC5.12 (SDOUT2/TDMIN), R161.2
I2S_SDOUT: R111.1, R112.1, R115.1, U7.25 (GPIO23)
I2S_SDOUT_N: IC6.9 (DSDIN), R111.2
INLN: C147.1, R148.2
INLN1: R179.1, U4.6
INRN: C135.1, R146.2
INRN1: R178.1, U4.11
INT_TP: FPC2.3, R75.2, U7.83 (GPIO42)
IO8: R217.1, U7.8 (GPIO8)
IO9_W: C175.2, J11.5, J11.5-5 (5), R150.2
IO10_W_BUSY: C174.2, J11.6, J11.6-6 (6), R151.2
IO11_CSI_RESET: Q4.3 (D), R58.2, U7.12 (GPIO11)
LCD_AVDD_9V6: C92.1, C93.1, D005.2, D013.1, J21.9, P19.P$1, R166.2, R168.2
LCD_BK_EN: R160.1, U6.4 (4-EN), U7.61 (GPIO31)
LCD_BK_POWER: Q11.1 (G), R180.1, U7.58 (GPIO29)
LCD_BK_VDD: C13.1, C17.2, L5.1, Q11.3 (D), R184.2, U6.6 (6-VIN)
LCD_RESET: J21.27, R69.2, U7.82 (GPIO41)
LCD_VCOM_3V3: C94.1, C95.1, J21.30, P20.P$1, R168.1, R169.2
LCD_VDD: C37.2, C38.2, C52.2, C53.2, IC4.5 (VOUT), J21.28, J21.29, R63.2, R65.1, R68.2, R122.2
LCD_VGH_18V: C99.1, C100.1, D016.1, J21.3, P18.P$1, R172.1, R173.2
LCD_VGL_-6V: C110.1, C111.1, D020.2, J21.4, P77.P$1, R174.1, R175.2
LED+: C18.1, C19.1, D003.-, D012.1, P63.P$1, R25.1, U6.5 (5-OV)
LED-: J21.7, J21.8, P64.P$1, R159.2, R163.2, U6.3 (3-FB)
MIC1N: C89.2
MIC1P: C101.2
MIC2N: C125.2, R141.2
MIC2P: C126.2, R142.2
MIC2_1: R132.2, R142.1, U176.1
MIC2_2: R131.1, R141.1, R145.1, R171.1, U176.2
MIC2_3: R134.1, R144.2, U176.3
MIC2_VDD_3V3: C72.2, FB6.2, U176.4
MIC3N: C124.1, R170.2
MIC3P: C123.1, R177.2
MIC_L/R: R131.2, U7.22 (GPIO20)
MIC_MCLK: R127.2, R134.2
MIC_SD2: R132.1, R162.2
unnamed: R1.1, U9.1 (EN)
unnamed: L1.1, U9.3 (SW)
unnamed: FB7.1, U4.12
unnamed: FB10.1, U13.8 (VOP)
unnamed: R6.1, U1.1 (UD+)
unnamed: R7.1, U1.2 (UD-)
unnamed: R5.1, U8.2 (B1)
unnamed: R9.1, U8.5 (B2)
unnamed: J1.B5, R3.2
unnamed: R8.2, U1.9 (RXD)
unnamed: R10.2, U1.8 (TXD)
unnamed: R16.2, U2.6 (PRO)
unnamed: C26.1, R2.2, R11.1, U9.5 (FB)
unnamed: L6.1, U10.3 (SW)
unnamed: C151.2, IC7.3 (CE), R181.1
unnamed: R13.1, R210.2, U10.1 (EN)
unnamed: C143.2, U4.10
unnamed: R185.2, U4.8
unnamed: D1.3, R31.1, R121.1
unnamed: D1.4, R32.1, R120.1
unnamed: D14.+, R26.1
unnamed: J21.1, J21.2, R25.2
unnamed: C173.2, J9.1, J9.1-1 (1), R49.1
unnamed: C176.2, J11.1, J11.1-1 (1), R48.1
unnamed: FB8.1, U4.14
unnamed: Q5.4 (4_G), R78.1, SW1.2 (2_COM2), SW1.5 (5_COM1)
unnamed: J1.A5, R4.1
unnamed: R79.1, U4.16
unnamed: C28.1, R24.1, R210.1, U10.4 (VIN)
unnamed: R150.1, U7.10 (GPIO9)
unnamed: R190.2, U7.40 (DSI_DATAN0)
unnamed: R92.2, U7.39 (DSI_DATAP0)
unnamed: C30.1, R35.1, U7.1 (GPIO1), Y4.2
unnamed: C29.1, R35.2, U7.104 (GPIO0), Y4.1
unnamed: R95.2, U7.36 (DSI_DATAN1)
unnamed: R99.2, U7.35 (DSI_DATAP1)
unnamed: R100.2, U7.37 (DSI_CLKN)
unnamed: C147.2, R179.2
unnamed: R102.2, U7.38 (DSI_CLKP)
unnamed: R103.2, U7.78 (FB_DCDC)
unnamed: R104.2, U7.34 (DSI_REXT)
unnamed: C21.2, IC4.3 (CE), R53.1
unnamed: C135.2, R178.2
unnamed: FB2.1, U3.8 (VOP)
unnamed: FB11.1, U13.5 (VON)
unnamed: FB3.1, U3.5 (VON)
unnamed: R117.1, U3.1 (CTRL)
unnamed: R118.2, U14.12 (P3.1/ADC9)
unnamed: R119.2, U14.11 (P3.0/ADC8)
unnamed: R139.1, R143.2, U13.1 (CTRL)
unnamed: IC5.3 (CDATA), R124.2
unnamed: IC5.4 (CCLK), R125.2
unnamed: FB9.1, U4.3
unnamed: C155.2, IC8.3 (CE), R116.1
unnamed: C159.2, R187.2, U14.7 (NRST/PWM6/P5.4)
unnamed: R151.1, U7.11 (GPIO10)
unnamed: FB12.1, U4.5
unnamed: C124.2, IC5.32 (MIC3N)
unnamed: C89.1, IC5.15 (MIC1N)
unnamed: C101.1, IC5.16 (MIC1P)
unnamed: R332.1, U7.7 (GPIO7)
unnamed: R216.1, U7.6 (GPIO6)
unnamed: R158.1, U7.48 (CSI_REXT)
unnamed: R157.1, U7.44 (CSI_CLKP)
unnamed: R156.1, U7.45 (CSI_CLKN)
unnamed: R155.1, U7.47 (CSI_DATAP1)
unnamed: R154.1, U7.46 (CSI_DATAN1)
unnamed: R152.1, U7.42 (CSI_DATAN0)
unnamed: J16.B5, R96.2
unnamed: J16.A5, R101.1
unnamed: C123.2, IC5.31 (MIC3P)
unnamed: C122.2, IC5.30 (REFQ34)
unnamed: C121.2, IC5.29 (REFP34)
unnamed: C76.2, IC2.3 (CE), R61.1
unnamed: C81.2, IC3.3 (CE), R66.1
unnamed: C86.2, R67.1, Y3.1 (1_EN)
unnamed: C120.2, IC5.28 (MIC4P)
unnamed: C119.2, IC5.27 (MIC4N)
unnamed: C118.2, IC5.26 (MICBIAS34)
unnamed: C117.2, IC5.25 (REFQM)
unnamed: C129.1, IC5.24 (MICBIAS12)
unnamed: C125.1, IC5.20 (MIC2N)
unnamed: C126.1, IC5.19 (MIC2P)
unnamed: C127.1, IC5.18 (REFQ12)
unnamed: C128.1, IC5.17 (REFP12)
unnamed: R147.2, U4.1
unnamed: C97.2, D017.1, D018.2
unnamed: IC5.1 (AD0), R73.2
unnamed: IC5.2 (AD1), R72.2
unnamed: C139.1, IC6.14 (DACVREF)
unnamed: C137.2, IC6.16 (VMID)
unnamed: C138.1, IC6.15 (ADCVREF)
unnamed: C140.1, IC6.13 (OUTN)
unnamed: C141.1, IC6.12 (OUTP)
unnamed: C142.1, FB13.1, IC6.11 (AVDD)
unnamed: D003.+, D012.2, L5.2, U6.1 (1-SW)
unnamed: C96.1, C97.1, D013.2, L2.2, U16.1 (1_SW)
unnamed: R165.2, U16.4 (4_EN)
unnamed: C96.2, D005.1, D015.2
unnamed: C93.2, R166.1, R167.2, U16.3 (3_FB)
unnamed: C98.1, D015.1, R172.2
unnamed: C140.2, R146.1, R170.1
unnamed: C109.1, D017.2, R174.2
unnamed: C141.2, R148.1, R177.1
P4_IO2: J7.9, U7.2 (GPIO2)
P4_IO3: J7.11, U7.3 (GPIO3)
P4_IO4: J7.13, U7.4 (GPIO4)
P4_IO5: J7.15, U7.5 (GPIO5)
P4_IO25: J7.17, U7.53 (GPIO25)
P4_IO35: R55.2, U7.66 (GPIO35)
P4_IO36: R60.2, U7.68 (GPIO36)
P4_IO39: R90.2, U7.80 (GPIO39)
P4_IO43: R88.2, U7.84 (GPIO43)
P4_IO44: R89.2, U7.86 (GPIO44)
P4_IO49: J7.19, U7.92 (GPIO49)
P4_IO50: J7.20, U7.93 (GPIO50)
P4_IO51: J7.18, U7.94 (GPIO51)
P4_IO52: J7.16, U7.95 (GPIO52)
P4_IO53: J7.14, U7.97 (GPIO53)
P4_IO54: J7.12, U7.98 (GPIO54)
P4_RST_EN: C35.2, K4.2, R54.2, U7.103 (CHIP_PU), U8.6 (C1)
P4_RXD2: R48.2, U7.57 (GPIO28)
P4_TXD2: R49.2, U7.56 (GPIO27)
P4_VBAT: C9.1, C42.2, R20.1, U7.102 (VBAT)
POWER_CHRG: R50.1, R120.2, U2.1 (CHG), U14.14 (P3.3/ADC11)
POWER_DONE: R47.1, R121.2, U2.5 (STD), U14.15 (P3.4/ADC11)
POWER_G_LED: R31.2, U14.17 (P3.6/ADC14)
POWER_R_LED: R32.2, U14.16 (P3.5/ADC13)
RESET_TP: FPC2.6, R74.2, U7.81 (GPIO40)
RTS: R9.2, U1.6 (RTS#), U8.1 (E1)
RXD0: R10.1, U7.70 (GPIO38)
RXD1: J2.1, P39.P$1, U7.90 (GPIO48)
RXD3: Q2.2 (S), R45.2, U7.64 (GPIO33)
SD1_CMD: C166.2, J5.3 (DI), P8.P$1, R28.1, R89.1
SD1_D0: C168.2, J5.7 (DO), P6.P$1, R27.1, R90.1
SD1_SCK: C167.2, J5.5 (SCLK), P7.P$1, R88.1, R140.1
SD2_CLK: R34.1, U7.19 (GPIO18)
SD2_CMD: R133.1, U7.20 (GPIO19)
SD2_D0: R135.1, U7.18 (GPIO17)
SD2_D1: R136.1, U7.17 (GPIO16)
SD2_D2: R137.1, U7.16 (GPIO15)
SD2_D3: R138.1, U7.15 (GPIO14)
SDCS: C165.2, J5.2 (CS), P57.P$1, R29.1, R33.1
SHLR: J21.6, R122.1, R123.2
SPI2_MISO: C171.2, J9.3, J9.3-3 (3), R332.2
SPI2_MOSI: C170.2, J9.4, J9.4-4 (4), R216.2
SPI2_SCK: C172.2, J9.2, J9.2-2 (2), R217.2
SPI_BOOT: C54.2, K3.2, R55.1, R91.2, U8.3 (C2)
STBYB: J21.26, R63.1, R64.2
STC8_RXD: J8.2, R119.1
STC8_TXD: J8.1, R118.1
STC8_VDD_3V3: C69.2, C156.2, C157.2, IC8.5 (VOUT), J8.3, R187.1, U14.8 (VCC), U14.9 (VREF)
TXD0: R8.1, U7.69 (GPIO37)
TXD1: J2.2, P38.P$1, U7.89 (GPIO47)
TXD3: Q1.2 (S), R52.2, U7.65 (GPIO34)
UART_IN_RXD3: J10.2, P67.P$1, Q2.3 (D), R46.2
UART_IN_TXD3: J10.1, P68.P$1, Q1.3 (D), R51.2
UPDN: J21.5, R68.1, R108.2
USB1_D+: J1.A6, J1.B6, P2.P$1, R6.2
USB1_D-: J1.A7, J1.B7, P3.P$1, R7.2
USB2_D+: J16.A6, J16.B6, U7.50 (DP)
USB2_D-: J16.A7, J16.B7, U7.49 (DM)
VBAT: C4.2, J3.P$1, P9.P$1, Q3.5 (5_D), Q3.6 (6_D), Q3.7 (7_D), Q3.8 (8_D), Q3.9 (9_D), R17.1, R164.1, U2.3 (BAT)
VCC5V: C136.2, C144.2, D1.1, D1.2, D2.-, D007.-, D10.-, IC8.1 (VIN), P11.P$1, Q3.1 (1_S), Q3.2 (2_S), Q3.3 (3_S), Q5.1 (1_S), Q5.2 (2_S), Q5.3 (3_S), R78.2, R116.2
VCC5V_IN: C3.2, D4.-, D008.-, D11.-, Q3.4 (4_G), R17.2, R18.2, R47.2, R50.2, U2.4 (VCC)
VCCA: C43.1, C47.2, R23.1, U7.51 (VCCA)
VDD5V: C12.1, C74.2, C75.2, C79.2, C80.2, C90.1, C91.1, C149.2, C150.2, FB15.1, FB17.2, FB18.2, IC2.1 (VIN), IC3.1 (VIN), IC7.1 (VIN), J7.2, J7.4, J7.6, L2.1, L4.2, P5.P$1, Q5.5 (5_D), Q5.6 (6_D), Q5.7 (7_D), Q5.8 (8_D), Q5.9 (9_D), Q11.2 (S), R1.2, R24.2, R26.2, R61.2, R66.2, R165.1, R180.2, R181.2, R184.1, U9.4 (VIN), U16.5 (5_IN)
VDD5V_W: C88.1, J9.7, J9.7-7 (7), L4.1
VDDA: C7.1, C8.2, R19.1, U7.101 (VDDA)
VDDPST: C36.1, C55.1, R40.1, R110.1, U7.59 (VDDPST), U7.67 (VDDPST)
VDDPST_1: C73.1, C107.2, R36.1, U7.9 (VDDPST_1)
VDDPST_2: C41.1, C44.2, R37.1, U7.21 (VDDPST_2)
VDDPST_3: C45.1, C49.2, R38.1, U7.30 (VDDPST_3)
VDDPST_4: C50.1, C56.2, R39.1, U7.62 (VDDPST_4)
VDDPST_5: C60.1, C65.1, Q8.1 (G), Q9.1 (G), R69.1, R74.1, R75.1, R97.1, R98.1, R109.1, U7.85 (VDDPST_5)
VDDPST_6: C61.1, C71.2, R41.1, U7.96 (VDDPST_6)
VDDPST_DCDC: C5.1, C6.2, R12.1, U7.77 (VDDPST_DCDC)
VDDPST_LDO: C46.1, C48.2, R70.1, U7.75 (VDDPST_LDO)
VDD_1V2: C31.2, C32.2, L6.2, P24.P$1, R14.1, R42.2, R43.2, R44.2
VDD_3V3: C1.2, C10.2, C16.2, C20.2, C26.2, C27.2, FB16.1, FPC2.5, IC4.1 (VIN), J2.3, J5.4 (VDD), J7.1, J7.3, J7.5, J13.3, L1.2, L3.2, P13.P$1, P15.P$1, P17.P$1, Q1.1 (G), Q2.1 (G), Q10.2 (S), R2.1, R12.2, R15.2, R19.2, R20.2, R22.1, R23.2, R27.2, R28.2, R29.2, R30.2, R36.2, R37.2, R38.2, R39.2, R41.2, R45.1, R52.1, R53.2, R54.1, R58.1, R59.1, R65.2, R70.2, R71.2, R76.2, R91.1, R93.1, R94.1, R106.1, R107.2, R110.2, R140.2, U1.7 (VCC)
VDD_3V3_A: C70.1, C169.1, J9.5, J9.5-5 (5), L3.1
VDD_FLASH: C39.1, C40.1, C51.1, IC10.8 (VCC), R105.1, R107.1, R333.2
VDD_HP_0: C108.1, C112.2, R42.1, U7.26 (VDD_HP_0)
VDD_HP_2: C113.1, C114.2, R43.1, U7.76 (VDD_HP_2)
VDD_HP_3: C115.1, C116.2, R44.1, U7.91 (VDD_HP_3)
VDD_MIPI_DPHY: C62.1, C63.1, C64.1, R80.1, U7.41 (VDD_MIPI_DPHY)
VOLN: C106.2, FB11.2, FB12.2, J4.P$2, P55.P$1
VOLP: C105.2, FB9.2, FB10.2, J4.P$1, P54.P$1
VORN: C68.2, FB3.2, FB7.2, J6.P$2, P32.P$1
VORP: C67.2, FB2.2, FB8.2, J6.P$1, P26.P$1
XTAL_N: C34.2, U7.99 (XTAL_N), Y2.3 (CRYSTAL_2)
XTAL_P: C33.1, U7.100 (XTAL_P), Y2.1 (CRYSTAL_1)
XVCLK: C87.2, FPC3.11, Y3.3 (3_OUT)

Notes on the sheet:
BOOT
RESET
HIG: SPI Boot
LOW: Download Boot
HIG: ESP32-P4 Enable
LOW: ESP32-P4 Off
Power_LED
USB interface
USB TO UART
Battery and control
ESP32-C6
7.0 inch IPS interface
SD card
Wireless module
UART & I2C & GPIO extensions
PDM MIC
UART_5V_IN
I2C_OUT
UART0_OUT
ESP32-P4
ESP32-P4_POWER
CSI_Interface
I led=200mV/1.1=182mA
DSI_LED Driver
Audio_OUT
DC-DC:5V to 3V3
DC-DC:5V to 1V2
Power SW
LCD_POWER
Charge indicator control
Audio_ADC/DAC
LDO:5V to 3V3(AUDIO POWER)
Simulated microphone U176 usage LMA3526B381，Welding R142,R141,R145,R144, NC:R132,R134,R131,R171 The digital microphone U176 usage LMD3526B381，Welding R132,R134,R131,R171, NC:R142,R141,R145,R144

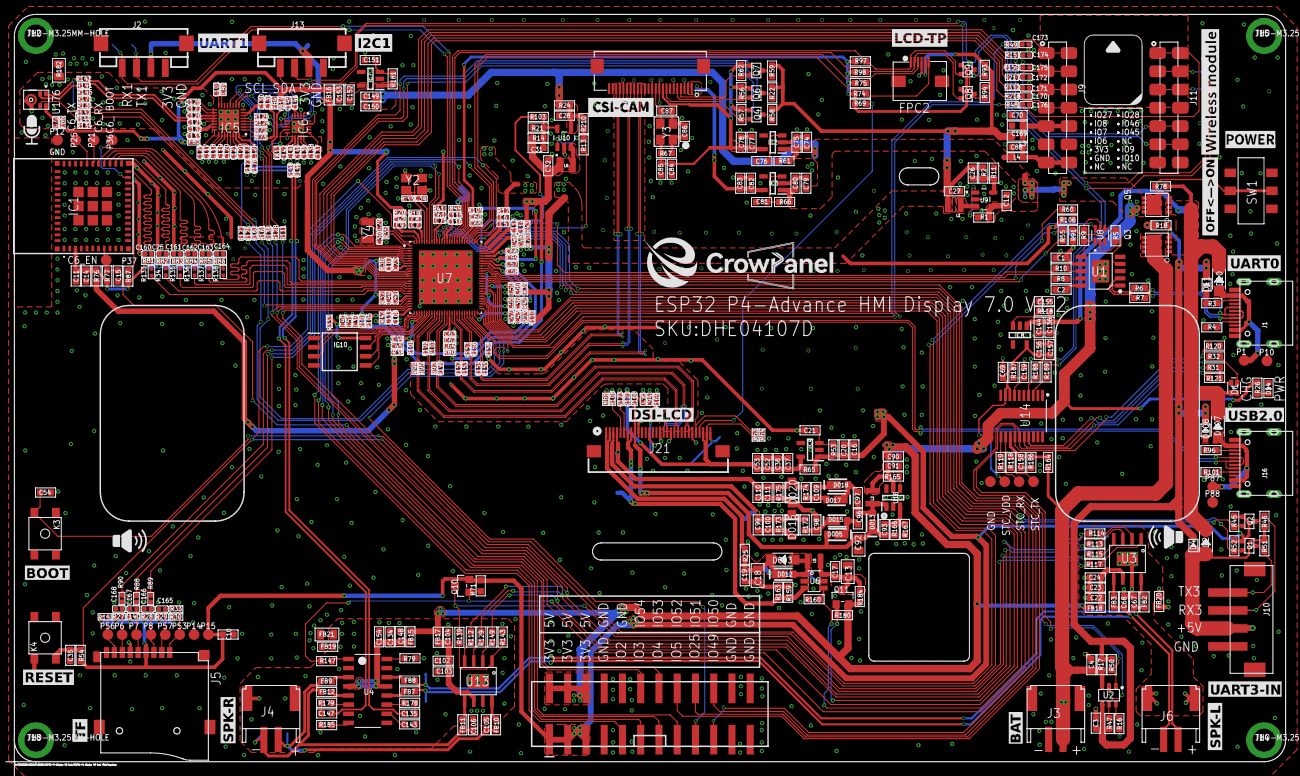
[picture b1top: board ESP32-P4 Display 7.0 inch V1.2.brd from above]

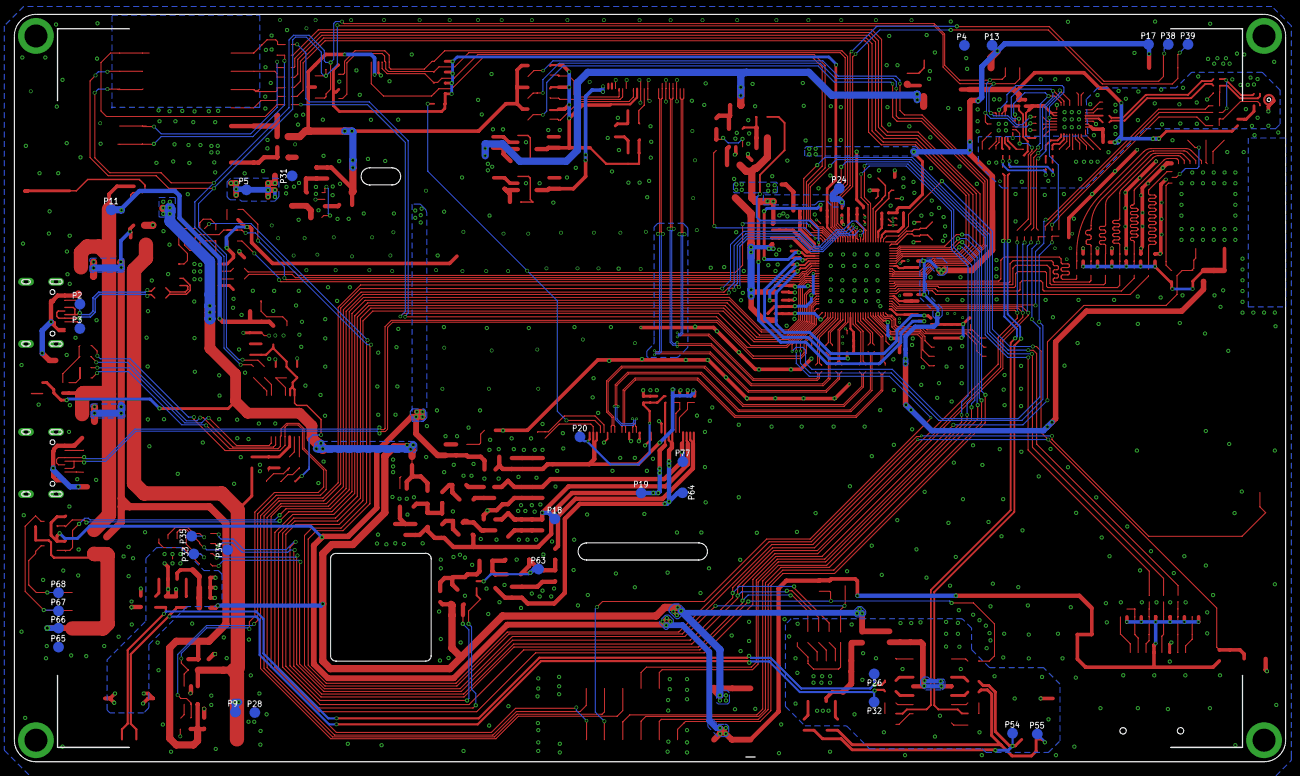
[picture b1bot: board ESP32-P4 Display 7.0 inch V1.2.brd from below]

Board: 2 copper layers, 176.9 x 104.0 mm, 519 parts (30 on the bottom side), 312 nets.

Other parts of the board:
U$113: P4-LCD-7.0-BK3

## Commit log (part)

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2026-05-12 sync lesson13
2026-06-04 sync example/V1.1 V1.2

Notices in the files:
parts and their libraries:
SparkFun-Coils: Licensing: Creative Commons ShareAlike 4.0 International - https://creativecommons.org/licenses/by-sa/4.0
